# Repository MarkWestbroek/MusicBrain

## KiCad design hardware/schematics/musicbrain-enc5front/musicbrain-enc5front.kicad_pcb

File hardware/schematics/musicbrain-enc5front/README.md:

# MusicBrain ENC5-FRONT — slim front: 5× encoder + 2 knoppen + display-expansie

**Praktisch:** vijf encoders en twee knoppen aan het paneel — de
menu- en parameterbediening van het systeem, via de i2criser aan de
bus.

**Status**: rev 2.0 — ERC 0, netlijst pad-voor-pad geverifieerd, DRC 0/0. Bord **30×110 mm**, 2 lagen.
**Riser**: `musicbrain-i2criser/` (domme I²C-doorlus; de generieke riser past NIET meer — rev 2.0 gebruikt de 1×10-front-koppeling).

## Wat het is

Slim front-bord (route 2): ligt plat aan het paneel, met **2× MCP23017**
(I²C, 32 GPIO-bits) erop. Bedient:

- **5× EC11E-encoder** (verticaal, met drukas — **drukassen zijn bedraad**)
  op de as-hartlijn 8,0 mm, steek **17,6 mm** → paneelknoppen tot ~17 mm;
- **2× drukknopje** (6 mm THT-tact) onder de encoders, ook op de hartlijn;
- **J2 = 2×8 expansieheader** (male, achterzijde) voor het **display-deel**:
  2 extra encoders + 4 knoppen + 2 reservelijnen, via bandkabel.

Dit front zit **uiterst links of rechts** in het paneel: daarom mag het
30 mm breed zijn (i.p.v. de 20 mm-kolom); de as-hartlijn blijft op 8,0.
De encoders zijn 90° gedraaid (pinnenrij horizontaal), zodat de
socketkolom over de hele bordlengte vrij is.

## Koppeling (front-koppel-standaard)

**J1 = 1×10 female socket op de ACHTERZIJDE**, kolom **x = 16,5 mm van de
westrand, pin 1 op 43,57 mm van de bovenrand** — identiek aan pot8front/
jack8/jack4. Contract ENC-front:

| pin | functie |
|----|----|
| 1 | GND |
| 2 | SDA |
| 3 | SCL |
| 4 | /IRQ |
| 5–9 | nc |
| 10 | +3V3 |

## GPIO-toewijzing (firmware-mapping)

**U1 = 0x20** (noord): GPA0–7 = E1A,E1B,E2A,E2B,E3A,E3B,E4A,E4B;
GPB0–3 = E1S..E4S (drukassen), GPB4/5 = X_SP1/X_SP2 (J2-spares), GPB6/7 vrij.

**U2 = 0x21** (zuid): GPA0–7 = X_E6A,X_E6B,X_E6S,X_E7A,X_E7B,X_E7S,X_K1,X_K2;
GPB0/1 = X_K3/X_K4, GPB2/3 = **K1/K2 (knopjes op dit bord)**,
GPB4–6 = E5A,E5B,E5S, GPB7 vrij.

**Firmware**: GPPU aan (alle ingangen, schakelaars schakelen naar GND);
INTA van beide chips deelt /IRQ → **IOCON.ODR = 1 (open-drain) + MIRROR**.

## J2-expansie (display-deel)

| pin | | pin | |
|----|----|----|----|
| 1 | GND | 2 | +3V3 |
| 3 | E6A | 4 | E6B |
| 5 | E6S | 6 | E7A |
| 7 | E7B | 8 | E7S |
| 9 | K1 | 10 | K2 |
| 11 | K3 | 12 | K4 |
| 13 | SP1 | 14 | SP2 |
| 15 | GND | 16 | GND |

(K1..K4/E6/E7 = knoppen/encoders **onder het display**; SP = reserve, op U1.)

## Routing & controlepunten

Koper via de freerouting-pijplijn (DSN → Docker-freerouting → SES native in
de generator), clearance **0,15 mm** (netclass in het .kicad_pro; JLC kan
0,127). X_E7S is een handroute (oostcorridor).

1. ⚠️ **QFN-pinvolgorde** (pin 1 = GPB1, EP = VSS, DS20001952) vóór
   assemblage-order nogmaals tegen de datasheet houden.
2. ⚠️ **Pin-1-oriëntatie** socket ↔ i2criser-J2 bij de eerste fysieke
   passing verifiëren.

## Aansluitoverzicht

### Pinouts

Bovenaanzicht van het bord (kijkend op de pinnen); pin 1 = vierkant. Gegenereerd uit het bordbestand met `hardware/kicad-generators/pinout_svg.py`.

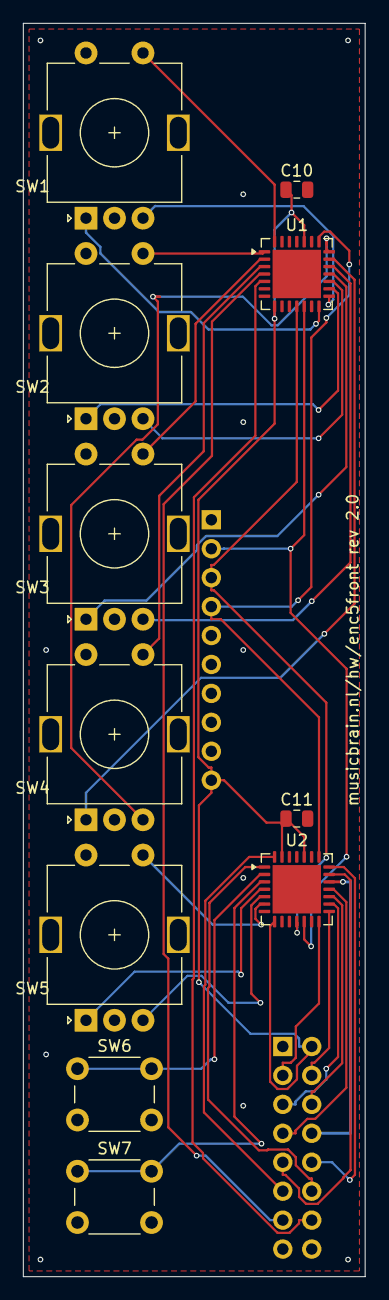
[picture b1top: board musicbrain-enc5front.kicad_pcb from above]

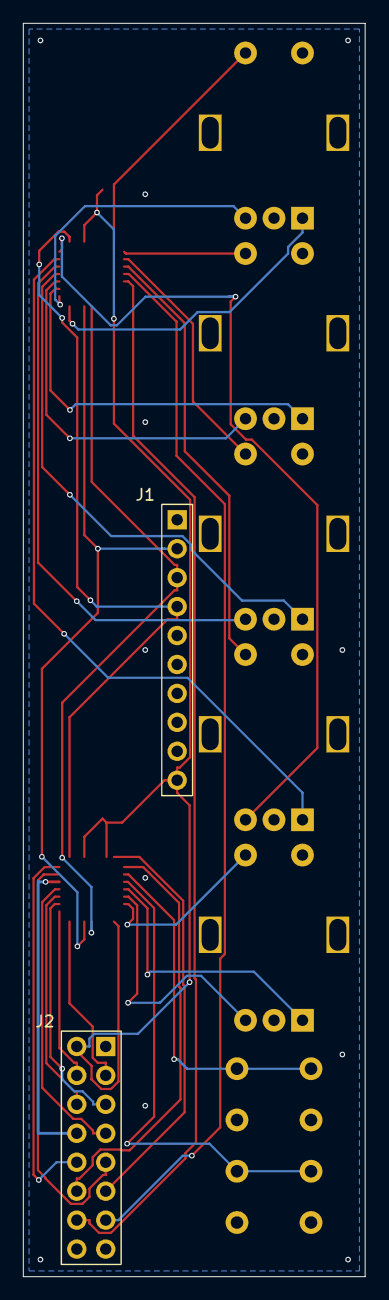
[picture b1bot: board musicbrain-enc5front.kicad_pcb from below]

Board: 2 copper layers, 30.0 x 110.0 mm, 13 parts (2 on the bottom side), 34 nets.

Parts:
C10, C11: 100n; C_0805_2012Metric
J1: Socket_1x10_backside
J2: Header_2x08_backside
SW1, SW2, SW3, SW4, SW5: EC11E; RotaryEncoder_Alps_EC11E-Switch_Vertical_H20mm
SW6, SW7: 6mm tact; SW_PUSH_6mm
U1, U2: MCP23017-E/ML; QFN-28-1EP_6x6mm_P0.65mm_EP4.25x4.25mm

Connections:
+3V3: C10.1, C11.1, J1.10, J2.2, U1.8, U1.24, U2.8, U2.24, U2.27
/E1A: SW1.A, U1.14
/E1B: SW1.B, U1.15
/E1S: SW1.S1, U1.28
/E2A: SW2.A, U1.16
/E2B: SW2.B, U1.17
/E2S: SW2.S1, U1.1
/E3A: SW3.A, U1.18
/E3B: SW3.B, U1.19
/E3S: SW3.S1, U1.2
/E4A: SW4.A, U1.20
/E4B: SW4.B, U1.21
/E4S: SW4.S1, U1.3
/E5A: SW5.A, U2.4
/E5B: SW5.B, U2.5
/E5S: SW5.S1, U2.6
/IRQ: J1.4, U1.22, U2.22
/K1: SW6.1, U2.2
/K2: SW7.1, U2.3
/SCL: J1.3, U1.11, U2.11
/SDA: J1.2, U1.12, U2.12
/X_E6A: J2.3, U2.14
/X_E6B: J2.4, U2.15
/X_E6S: J2.5, U2.16
/X_E7A: J2.6, U2.17
/X_E7B: J2.7, U2.18
/X_E7S: J2.8, U2.19
/X_K1: J2.9, U2.20
/X_K2: J2.10, U2.21
/X_K3: J2.11, U2.28
/X_K4: J2.12, U2.1
/X_SP1: J2.13, U1.4
/X_SP2: J2.14, U1.5
GND: C10.2, C11.2, J1.1, J2.1, J2.15, J2.16, SW1.C, SW1.S2, SW2.C, SW2.S2, SW3.C, SW3.S2, SW4.C, SW4.S2, SW5.C, SW5.S2, SW6.2, SW7.2, U1.9, U1.25, U1.26, U1.27, U1.29, U2.9, U2.25, U2.26, U2.29

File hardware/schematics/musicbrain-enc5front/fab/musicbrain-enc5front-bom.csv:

"Comment","Designator","Footprint","LCSC Part #"
"100n","C10,C11","C_0805_2012Metric","C49678"
"NAAR I2C-RISER (achterzijde)","J1","Socket_1x10_backside",""
"DISPLAY-EXPANSIE (achterzijde)","J2","Header_2x08_backside",""
"EC11E (switch)","SW1,SW2,SW3,SW4,SW5","RotaryEncoder_Alps_EC11E-Switch_Vertical_H20mm",""
"6mm tact","SW6,SW7","SW_PUSH_6mm",""
"MCP23017-E/ML (0x20)","U1","QFN-28-1EP_6x6mm_P0.65mm_EP4.25x4.25mm","C639770"
"MCP23017-E/ML (0x21)","U2","QFN-28-1EP_6x6mm_P0.65mm_EP4.25x4.25mm","C639770"

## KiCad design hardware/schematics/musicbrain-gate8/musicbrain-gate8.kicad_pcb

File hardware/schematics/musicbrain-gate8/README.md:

# MusicBrain GATE8 — 8× gate-uitgang (slotkaart)

**Praktisch:** acht gate/trigger-uitgangen. Start envelopes, klokt
sequencers en triggert extern gear vanuit de software — 0–5 V per
kanaal met serieweerstand. Combineer met een jack8 als front.

**Status**: rev 2.0 — ERC 0, netlijst pad-voor-pad geverifieerd, DRC 0/0.
**Spec**: `doc/spi-bus-spec.md` v2.0. Bord **55 × 45 mm**, 2 lagen.

## Gen 2 (rev 2.0, 2026-07-16)

- Slot **2×12**; H 80 → 45; 74HCT595 met de Q-uitgangen noordwaarts
  naar de 1k-kolommen. J2-contract en bitvolgorde ongewijzigd.
- Generator geport naar cardlib (`gen_gate.py`); koper via freerouting.

De schakelingbeschrijving hieronder is ongewijzigd; waar de lopende
tekst nog gen-1-maten of 2×10 noemt, geldt bovenstaande. Overzicht en
pinouts hieronder zijn gen-2-gegenereerd.

## Wat het is

De simpelste kaart van de familie: 8 digitale gate/trigger-uitgangen (0–5V)
uit één **74HCT595 schuifregister**. Geen microcontroller nodig — SPI *is*
een schuifregisterprotocol, dus de 595 is zelf de ontvanger:

| 595-pin | Buslijn | Werking |
|---|---|---|
| SER (14) | MOSI | databits schuiven binnen |
| SRCLK (11) | SCLK | klok per bit |
| RCLK (12) | CS (slotpin 13) | **stijgende flank van CS** kopieert alle 8 bits tegelijk naar de uitgangen |
| ~OE (13) | GND | uitgangen altijd actief |
| ~SRCLR (10) | +5V | nooit hardware-clear |

Firmware: `SPI.beginTransaction(mode 0)` → CS laag → `SPI.transfer(bits)` →
CS hoog → alle acht gates staan er glitch-vrij en gelijktijdig op.
Bit 0 = QA = GATE1 … bit 7 = QH = GATE8.

## Ontwerpkeuzes

- **HCT-variant op 5V**: TTL-drempels, dus de 3,3V-bussignalen zijn ruim
  voldoende, terwijl de uitgangen echte 0–5V gates leveren (Eurorack-drempel
  ~1–2V). De 5V komt lokaal van een AMS1117-5.0 uit de +12V-rail.
- **1 kΩ serie per uitgang**: kortsluit-/kabelbescherming.
- Buspinnen MISO, LDAC, I2C, IRQ, SPARE's en −12V zijn bewust niet
  aangesloten (write-only kaart).
- SPI-mode 0 (de AD5754 gebruikt mode 1 — de Teensy wisselt per transactie
  via `SPISettings`, zie spec regel 4).

## Aansluitingen

- **J1** (haakse male 2×10, onderrand): het bus-slotcontract uit de spec.
  Pennen steken 6 mm onder de kaartrand uit, het slot-socket in.
- **J2** (haakse male 1×10, bovenrand): 1 = GND, 2–9 = GATE1..8, 10 = GND.
  Zelfde contract als de ADC8-kaart → één jack8-printje past op beide.
  J2 staat **recht boven het midden van J1** (spec-standaard), zodat de
  jack-strips van alle kaarten op de bovenplaat uitlijnen.

## PCB-notities (v1.1)

Signaalstroom van onder naar boven: J1 (bus) → 74HCT595 → weerstandsrij →
J2 (paneel). De Q-uitgangen verlaten de chip via een via-kolom en lopen als
L-paden over B.Cu (oost, dan noord) naar hun weerstand — exits en doelen
staan in dezelfde volgorde, dus dat is kruisingsvrij; QA komt van de
oostkolom en loopt bovenlangs om de "Q-wal" heen. SCLK en CS hebben elk
één B.Cu-hop om de aanvoer vanaf J1 te ontvlechten. De AMS1117 met C1–C3
zit in de zuidoosthoek; +5V loopt via één B.Cu-run (y=157,5) naar VCC,
~SRCLR en de condensatoren. GND via vlakken op beide lagen + stitching-via's.

## Uitbreidingsideeën (v2)

- LED + weerstand per gate (visuele feedback).
- TPIC6B595 i.p.v. HCT595 voor 10V-gates of zwaardere belasting.
- Tweede 595 in ketting (QH' → SER) voor 16 gates met dezelfde CS.

## Aansluitoverzicht

### Pinouts

Bovenaanzicht van het bord (kijkend op de pinnen); pin 1 = vierkant. Gegenereerd uit het bordbestand met `hardware/kicad-generators/pinout_svg.py`.

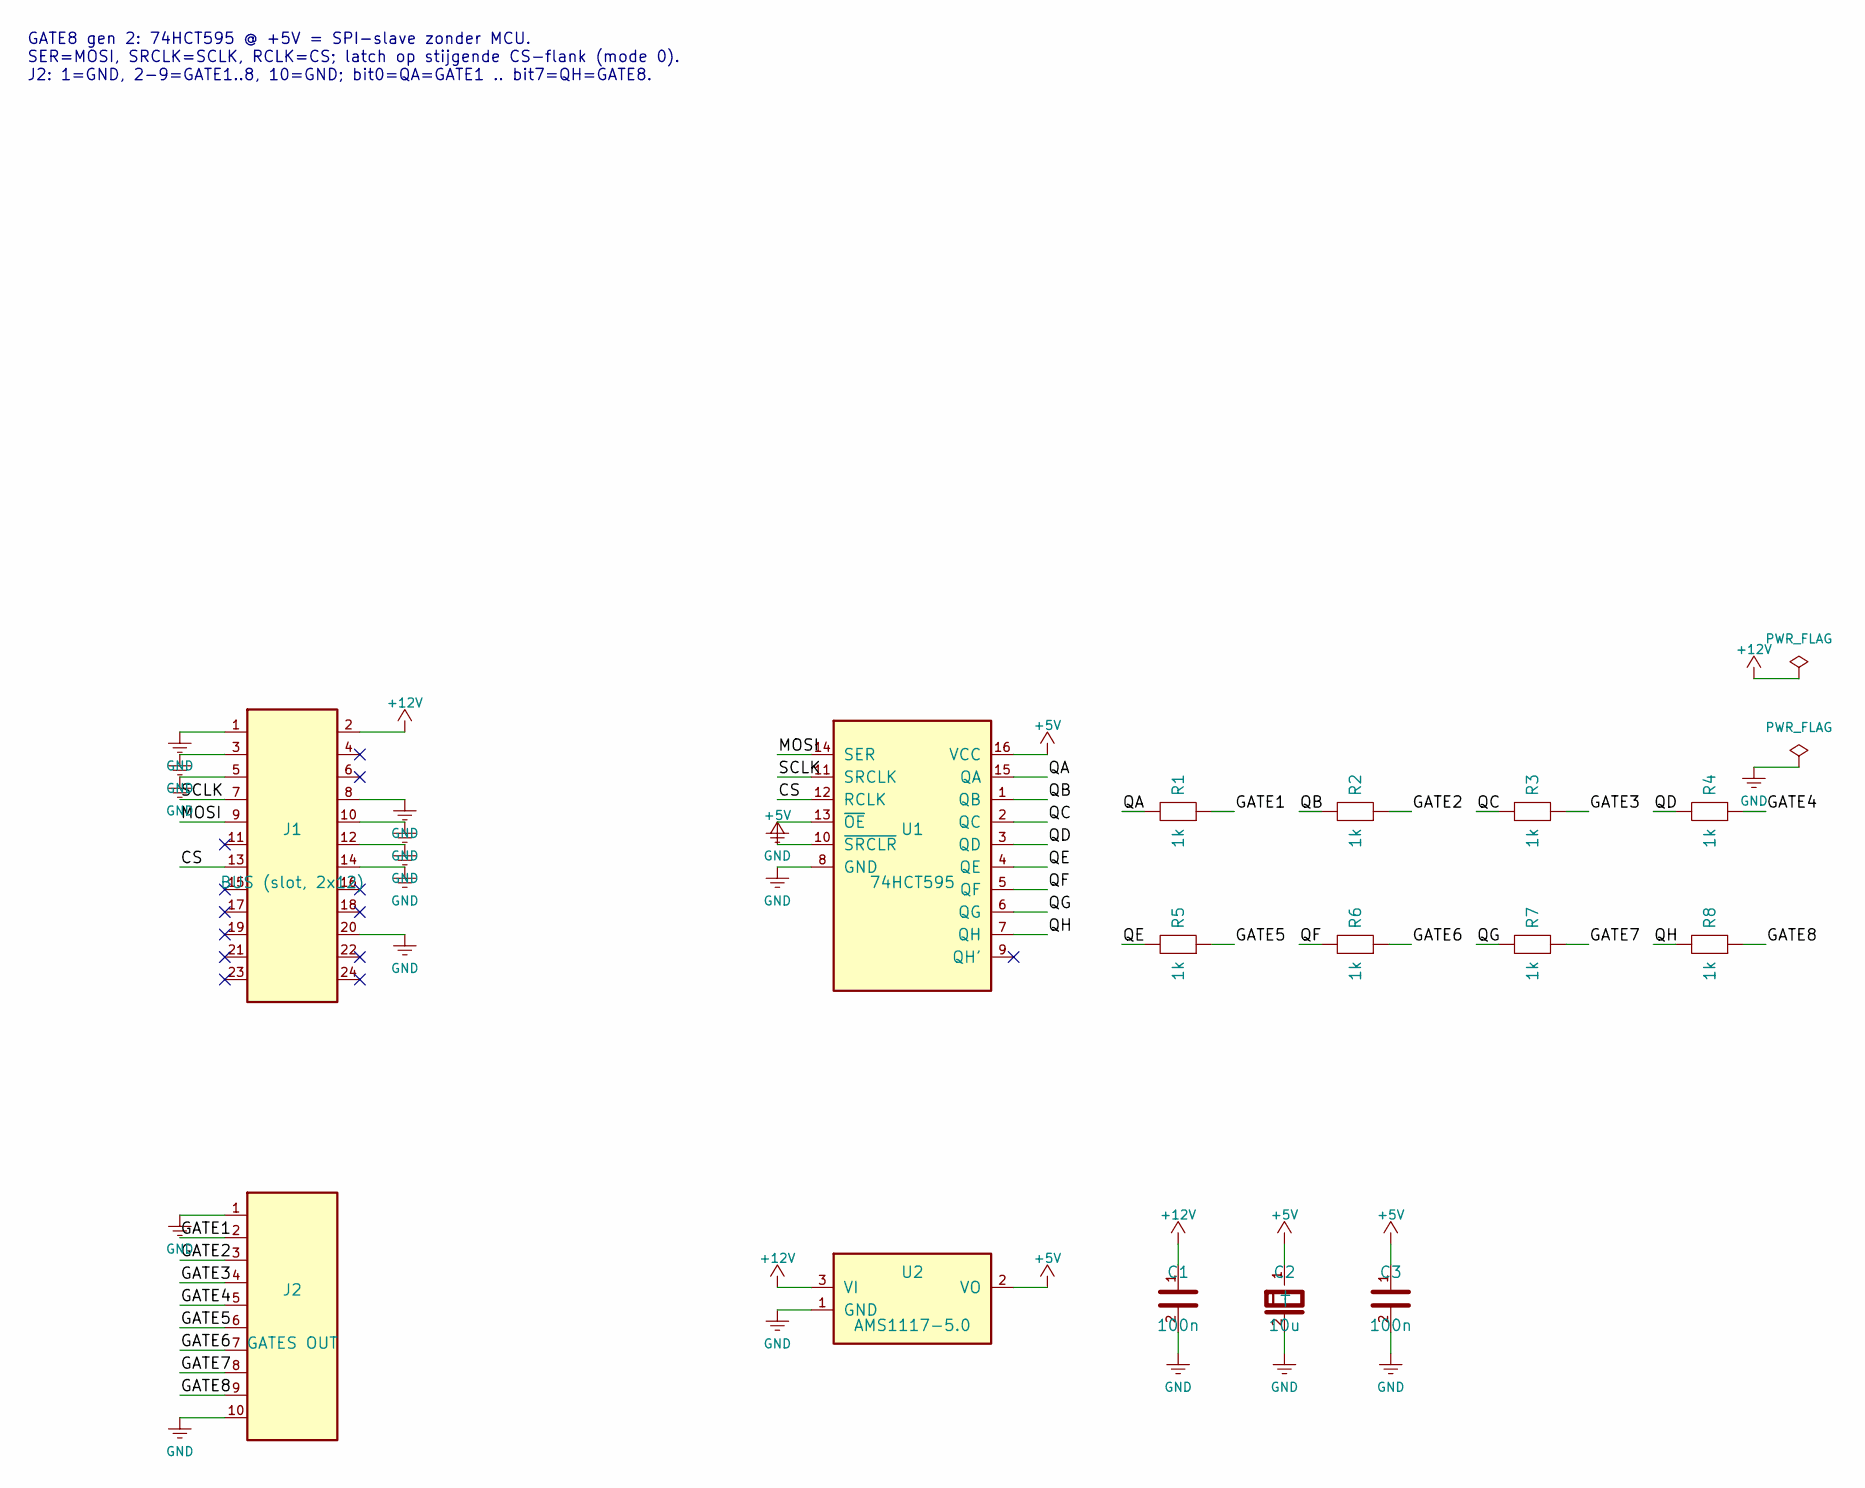
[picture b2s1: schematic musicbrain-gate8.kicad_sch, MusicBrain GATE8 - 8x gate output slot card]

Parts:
C1, C3: 100n; C_0805_2012Metric
C2: 10u; CP_Elec_4x5.3
J1: BUS (slot, 2x12); PinHeader_2x12_P2.54mm_Horizontal
J2: GATES OUT; PinHeader_1x10_P2.54mm_Horizontal
R1, R2, R3, R4, R5, R6, R7, R8: 1k; R_0805_2012Metric
U1: 74HCT595; SOIC-16_3.9x9.9mm_P1.27mm
U2: AMS1117-5.0; SOT-223-3_TabPin2

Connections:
+5V: C2.1 (+), C3.1, U1.10 (~SRCLR), U1.16 (VCC), U2.2 (VO)
+12V: C1.1, J1.2, U2.3 (VI)
/CS: J1.13, U1.12 (RCLK)
/GATE1: J2.2, R1.2
/GATE2: J2.3, R2.2
/GATE3: J2.4, R3.2
/GATE4: J2.5, R4.2
/GATE5: J2.6, R5.2
/GATE6: J2.7, R6.2
/GATE7: J2.8, R7.2
/GATE8: J2.9, R8.2
/MOSI: J1.9, U1.14 (SER)
/QA: R1.1, U1.15 (QA)
/QB: R2.1, U1.1 (QB)
/QC: R3.1, U1.2 (QC)
/QD: R4.1, U1.3 (QD)
/QE: R5.1, U1.4 (QE)
/QF: R6.1, U1.5 (QF)
/QG: R7.1, U1.6 (QG)
/QH: R8.1, U1.7 (QH)
/SCLK: J1.7, U1.11 (SRCLK)
GND: C1.2, C2.2 (-), C3.2, J1.1, J1.3, J1.5, J1.8, J1.10, J1.12, J1.14, J1.20, J2.1, J2.10, U1.8 (GND), U1.13 (~OE), U2.1 (GND)

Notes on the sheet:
GATE8 gen 2: 74HCT595 @ +5V = SPI-slave zonder MCU. SER=MOSI, SRCLK=SCLK, RCLK=CS; latch op stijgende CS-flank (mode 0). J2: 1=GND, 2-9=GATE1..8, 10=GND; bit0=QA=GATE1 .. bit7=QH=GATE8.

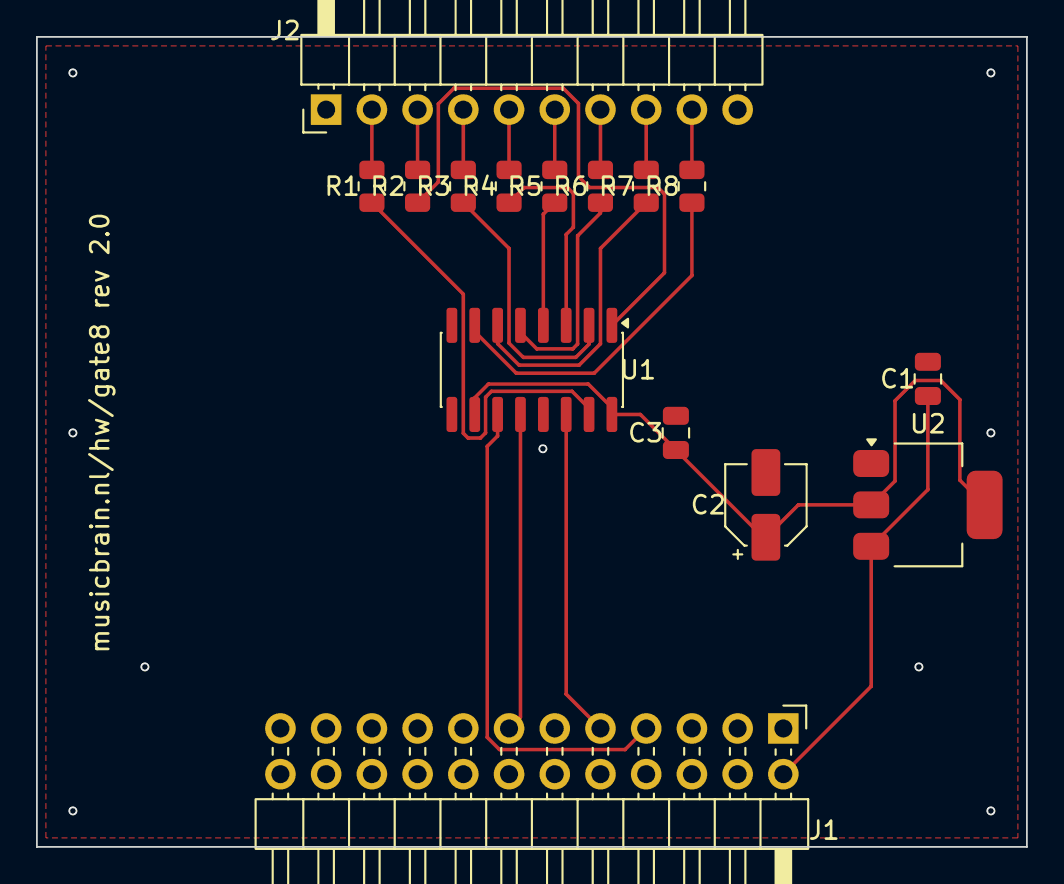
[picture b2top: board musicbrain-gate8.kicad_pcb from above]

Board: 2 copper layers, 55.0 x 45.0 mm, 15 parts (0 on the bottom side), 22 nets.

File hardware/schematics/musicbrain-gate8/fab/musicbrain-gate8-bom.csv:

"Comment","Designator","Footprint","LCSC Part #"
"100n","C1,C3","C_0805_2012Metric","C49678"
"10u","C2","CP_Elec_4x5.3",""
"BUS","J1","PinHeader_2x10_P2.54mm_Horizontal",""
"GATES OUT","J2","PinHeader_1x10_P2.54mm_Horizontal",""
"1k","R1,R2,R3,R4,R5,R6,R7,R8","R_0805_2012Metric","C17513"
"74HCT595","U1","SOIC-16_3.9x9.9mm_P1.27mm","C282339"
"AMS1117-5.0","U2","SOT-223-3_TabPin2","C6187"

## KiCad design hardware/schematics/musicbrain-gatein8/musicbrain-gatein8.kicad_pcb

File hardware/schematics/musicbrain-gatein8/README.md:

# MusicBrain GATEIN8 — 8× gate/trigger-ingang (slotkaart)

**Praktisch:** acht gate/trigger-ingangen. Leest externe klokken,
triggers en voetschakelaars de software in, met ingangsbeveiliging en
een gedefinieerd rustniveau per kanaal. Combineer met een jack8.

**Status**: rev 2.0 — ERC 0, netlijst pad-voor-pad geverifieerd, DRC 0/0.
**Spec**: `doc/spi-bus-spec.md` v2.0. Bord **50 × 45 mm**, 2 lagen.

## Gen 2 (rev 2.0, 2026-07-16)

- Slot **2×12** via `bus.j1_map`; H 80 → 45; kanaalkolommen recht onder
  de J2-pinnen. D_OF_IN-mapping (firmware-contract) ongewijzigd.
- Koper via freerouting; GND via de vlakken + hechtvia's.

De schakelingbeschrijving hieronder is ongewijzigd; waar de lopende
tekst nog gen-1-maten of 2×10 noemt, geldt bovenstaande. Overzicht en
pinouts hieronder zijn gen-2-gegenereerd.

## Wat het is

8 digitale ingangen (gates, triggers, clocks) die de firmware in één
SPI-transactie binnenhaalt via een **74HC165** schuifregister (parallel-in,
serieel-uit) op +3V3. Elke ingang is Eurorack-proof geconditioneerd:

- **100 kΩ serie** (R1–R8): stroombegrenzing bij hete signalen;
- **100 kΩ pulldown** (R11–R18): ongepatcht = netjes laag;
- **BAT54S-clamp** (D1–D8): knoop geklemd tussen GND en +3V3 — ±10V mag
  er zo in (≤ ~70 µA clampstroom door de 100k).
- HC-drempel op 3V3 ≈ 1,65 V → alles boven ~2 V telt als hoog.

## Latch-truc (~PL vanaf CS)

De '165 laadt parallel zolang ~PL laag is en schuift pas als hij weer
hoog is — maar CS blijft laag tijdens de hele SPI-transactie. Daarom maakt
**C3 (220p) + R9 (10k naar 3V3)** van de CS-neerflank een korte
~PL-latchpuls (~2 µs): de kaart bevriest zijn 8 bits op CS↓, daarna klokt
de Teensy ze binnen. **Firmware: wacht ≥5 µs tussen CS-laag en de
transfer.** Q7 gaat via een **74LVC1G125** (OE = CS) naar MISO, zodat de
kaart de bus loslaat als hij niet geselecteerd is.

## Bitvolgorde

Routinggedreven mapping (firmware hertelt met een tabel), eerste bit
(Q7/D7) eerst: **IN6, IN5, IN4, IN3, IN1, IN2, IN7, IN8**.

## Aansluitingen

- **J1** (haakse male 2×10, onderrand): bus-slotcontract; alleen SCLK,
  MISO, CS en +3V3 gebruikt — MOSI/±12V nc.
- **J2** (haakse male 1×10, bovenrand): 1 = GND, 2–9 = IN1..8, 10 = GND —
  zelfde contract als GATE8/ADC8, dus hetzelfde jack8-printje past.
  **JP1 op het jack8-printje dichtsolderen** (inputs → ongepatcht 0 V).

## PCB-notities

Per kanaal een knoopkolom onder de serieweerstand: pulldown-tap opzij,
diode-pad-3 op de kolom (het spoor duikt tussen de diodepads 1/2 door).
De acht knopen bereiken de '165 via B.Cu-lanes: vier bovenlangs
(y 129–131,4) naar de noordrij, vier onderlangs (y 145–147,4) dwars
tussen de SOIC-padrijen door naar de zuidrij. De +3V3-spine loopt langs
de oostrand met B-aftakrijen voor de diodes (y 122,9/127,3), VCC (132,9)
en R9 (148,9). MISO duikt onder de J1-padrij door (B.Cu) het THT-pad in.

## Aansluitoverzicht

### Pinouts

Bovenaanzicht van het bord (kijkend op de pinnen); pin 1 = vierkant. Gegenereerd uit het bordbestand met `hardware/kicad-generators/pinout_svg.py`.

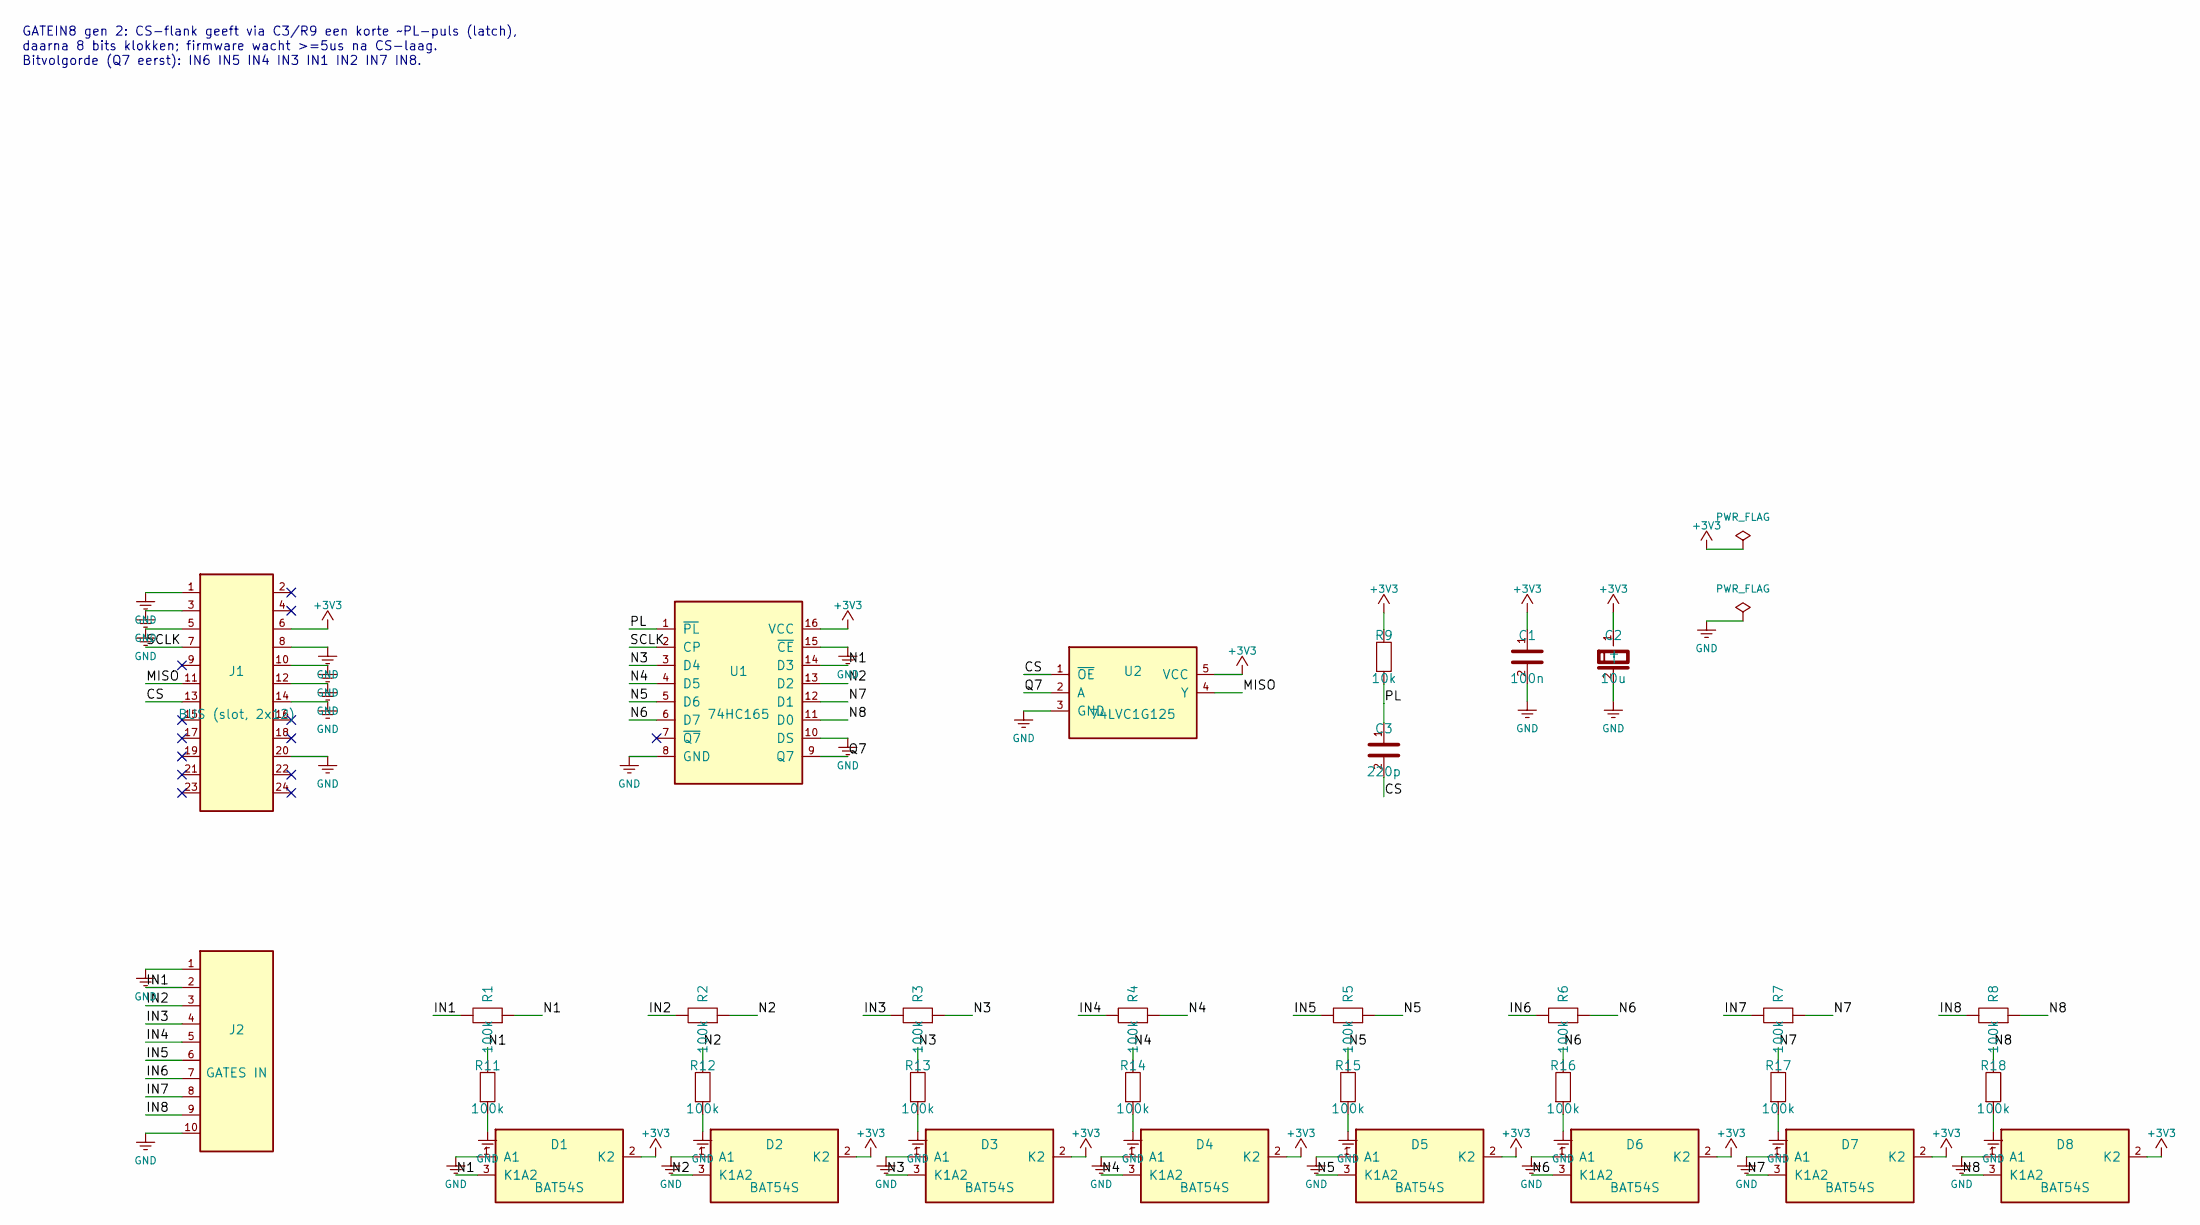
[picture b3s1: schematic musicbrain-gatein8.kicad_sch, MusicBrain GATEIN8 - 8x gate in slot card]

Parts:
C1: 100n; C_0805_2012Metric
C2: 10u; CP_Elec_4x5.3
C3: 220p; C_0805_2012Metric
D1, D2, D3, D4, D5, D6, D7, D8: BAT54S; SOT-23
J1: BUS (slot, 2x12); PinHeader_2x12_P2.54mm_Horizontal
J2: GATES IN; PinHeader_1x10_P2.54mm_Horizontal
R1, R2, R3, R4, R5, R6, R7, R8, R11, R12, R13, R14, R15, R16, R17, R18: 100k; R_0805_2012Metric
R9: 10k; R_0805_2012Metric
U1: 74HC165; SOIC-16_3.9x9.9mm_P1.27mm
U2: 74LVC1G125; SOT-23-5

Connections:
+3V3: C1.1, C2.1 (+), D1.2 (K2), D2.2 (K2), D3.2 (K2), D4.2 (K2), D5.2 (K2), D6.2 (K2), D7.2 (K2), D8.2 (K2), J1.6, R9.1, U1.16 (VCC), U2.5 (VCC)
/CS: C3.2, J1.13, U2.1 (~OE)
/IN1: J2.2, R1.1
/IN2: J2.3, R2.1
/IN3: J2.4, R3.1
/IN4: J2.5, R4.1
/IN5: J2.6, R5.1
/IN6: J2.7, R6.1
/IN7: J2.8, R7.1
/IN8: J2.9, R8.1
/MISO: J1.11, U2.4 (Y)
/N1: D1.3 (K1A2), R1.2, R11.1, U1.14 (D3)
/N2: D2.3 (K1A2), R2.2, R12.1, U1.13 (D2)
/N3: D3.3 (K1A2), R3.2, R13.1, U1.3 (D4)
/N4: D4.3 (K1A2), R4.2, R14.1, U1.4 (D5)
/N5: D5.3 (K1A2), R5.2, R15.1, U1.5 (D6)
/N6: D6.3 (K1A2), R6.2, R16.1, U1.6 (D7)
/N7: D7.3 (K1A2), R7.2, R17.1, U1.12 (D1)
/N8: D8.3 (K1A2), R8.2, R18.1, U1.11 (D0)
/PL: C3.1, R9.2, U1.1 (~PL)
/Q7: U1.9 (Q7), U2.2 (A)
/SCLK: J1.7, U1.2 (CP)
GND: C1.2, C2.2 (-), D1.1 (A1), D2.1 (A1), D3.1 (A1), D4.1 (A1), D5.1 (A1), D6.1 (A1), D7.1 (A1), D8.1 (A1), J1.1, J1.3, J1.5, J1.8, J1.10, J1.12, J1.14, J1.20, J2.1, J2.10, R11.2, R12.2, R13.2, R14.2, R15.2, R16.2, R17.2, R18.2, U1.8 (GND), U1.10 (DS), U1.15 (~CE), U2.3 (GND)

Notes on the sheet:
GATEIN8 gen 2: CS-flank geeft via C3/R9 een korte ~PL-puls (latch), daarna 8 bits klokken; firmware wacht >=5us na CS-laag. Bitvolgorde (Q7 eerst): IN6 IN5 IN4 IN3 IN1 IN2 IN7 IN8.

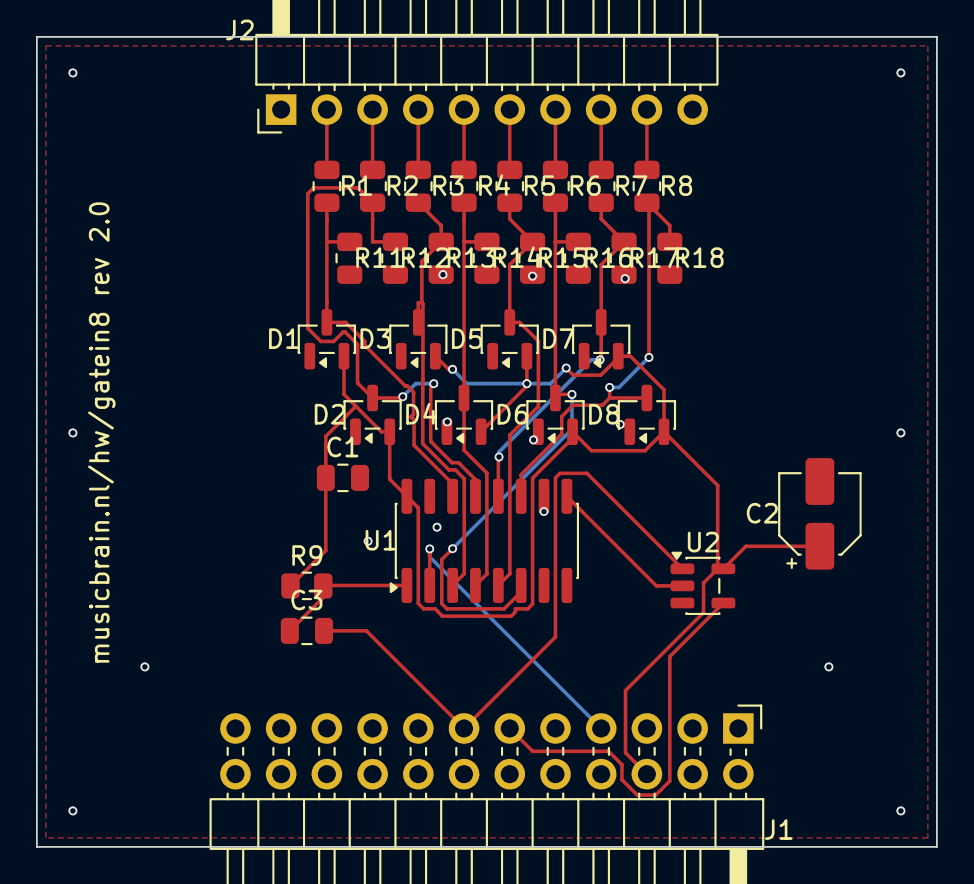
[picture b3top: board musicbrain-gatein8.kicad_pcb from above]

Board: 2 copper layers, 50.0 x 45.0 mm, 32 parts (0 on the bottom side), 23 nets.

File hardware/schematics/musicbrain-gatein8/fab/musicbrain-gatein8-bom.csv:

"Comment","Designator","Footprint","LCSC Part #"
"100n","C1","C_0805_2012Metric","C49678"
"10u","C2","CP_Elec_4x5.3","C3343"
"220p","C3","C_0805_2012Metric","C107145"
"BAT54S","D1,D2,D3,D4,D5,D6,D7,D8","SOT-23","C7420333"
"BUS","J1","PinHeader_2x10_P2.54mm_Horizontal","C19190505"
"GATES IN","J2","PinHeader_1x10_P2.54mm_Horizontal","C2687688"
"100k","R1,R2,R3,R4,R5,R6,R7,R8,R11,R12,R13,R14,R15,R16,R17,R18","R_0805_2012Metric","C149504"
"10k","R9","R_0805_2012Metric","C17414"
"74HC165","U1","SOIC-16_3.9x9.9mm_P1.27mm","C5613"
"74LVC1G125","U2","SOT-23-5","C12518"

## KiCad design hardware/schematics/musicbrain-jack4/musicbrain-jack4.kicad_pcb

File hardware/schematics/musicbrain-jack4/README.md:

# MusicBrain jack4 — Thonkiconn-paneeldrager (4 jacks)

**Praktisch:** 4-kanaals jack-breakout aan een kabel, voor CV-uit via
een hub-connector (bijv. de AD5754-breakout) — kost geen slot.

**Status**: rev 2.0 — ERC 0, netlijst geverifieerd, DRC 0/0. Bord **20 × 60 mm**.

## Gen 2 (rev 2.0, 2026-07-16)

- 4 jacks op steek **13,75**; kabelbord aan de hub-DAC (centrering van de
  socket is hier niet relevant).
- Zelfde pad-slanking en randmarge als jack8.

De schakelingbeschrijving hieronder is ongewijzigd; waar de lopende
tekst nog gen-1-maten of 2×10 noemt, geldt bovenstaande. Overzicht en
pinouts hieronder zijn gen-2-gegenereerd.
**Zusje: `musicbrain-jack8/` (8 jacks + 1×10 header).**

**v1.2 (2026-07-11)**: socket op de **front-koppel-standaard** (kolom x = 16,5
van de westrand, pin 1 op 43,57 van de bovenrand); 3D-model op de gatenrij;
silk-URL naar bordmidden; PCB-papier A3.

## Wat het is

Een passieve strip met **4× Thonkiconn** (PJ398SM = PJ301M-12 = WQP518MA,
onderling uitwisselbaar) op 15 mm steek, die als **frontpaneel-drager**
dient: de strip ligt horizontaal onder de bovenplaat, de schroefbussen steken erdoorheen en de moeren klemmen paneel
en printje op elkaar — geen extra steunen nodig.

## Aansluiting op de kaarten

- **J1** (1×6): 1 = GND, 2–5 = CH1..4, 6 = GND — hetzelfde contract als
  J2 op GATE8 én ADC8, dus één jack4 past op beide kaartsoorten.
- **Montage**: de female socket wordt op de **achterzijde** gesoldeerd
  (opening richting kaart); de kaart krijgt aan zijn frontrand een haakse
  male header. Het silkscreen op de achterzijde markeert de positie.
- Headerpositie: hart in het **midden van de strip**; de kaart heeft zijn
  paneelconnector recht boven het slotcentrum (spec-standaard), zodat elk
  jack-printje op elke kaart past en de strips op de bovenplaat uitlijnen.

## JP1: schakelcontact-normalling

Elke Thonkiconn heeft een schakelcontact (TN) dat bij een ongepatchte jack
tegen de tip ligt. Alle TN's zijn gebust naar één soldeerjumper **JP1**:

- **INPUT-kaart (ADC8): JP1 dichtsolderen** → ongepatchte ingangen lezen
  netjes 0 V.
- **OUTPUT-kaart (GATE8/DAC): JP1 OPEN laten!** Anders wordt elke
  ongepatchte uitgang via het schakelcontact naar GND kortgesloten
  (de 100R/1k serieweerstanden beperken dat, maar het hoort niet).

## Paneel

3U Eurorack: paneelhoogte 128,5 mm; boorpatroon = 4× Ø6 mm gat op 15 mm
steek, gecentreerd op de jackposities (eerste jack 8 mm van de bovenrand
van het printje). Printje zelf is 65 mm hoog (half 3U-paneel of 3U half gevuld).

## Aansluitoverzicht

### Pinouts

Bovenaanzicht van het bord (kijkend op de pinnen); pin 1 = vierkant. Gegenereerd uit het bordbestand met `hardware/kicad-generators/pinout_svg.py`.

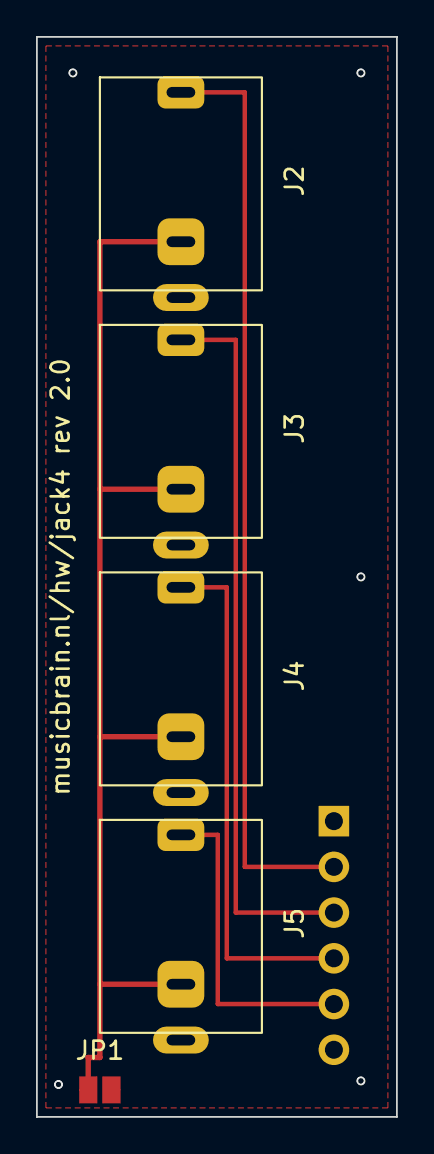
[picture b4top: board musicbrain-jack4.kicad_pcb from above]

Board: 2 copper layers, 20.0 x 60.0 mm, 6 parts (1 on the bottom side), 6 nets.

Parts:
J1: SOCKET-BACK; Header_1x06_backside
J2, J3, J4, J5: PJ398SM; Jack_3.5mm_PJ398SM_Thonkiconn
JP1: NORM=GND; SolderJumper-2_P1.3mm_Open_TrianglePad1.0x1.5mm

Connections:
/CH1: J1.2, J2.1
/CH2: J1.3, J3.1
/CH3: J1.4, J4.1
/CH4: J1.5, J5.1
/NORM: J2.3, J3.3, J4.3, J5.3, JP1.1
GND: J1.1, J1.6, J2.2, J3.2, J4.2, J5.2, JP1.2

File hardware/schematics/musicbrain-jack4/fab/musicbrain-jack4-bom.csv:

"Comment","Designator","Footprint","LCSC Part #"
"NAAR KAART","J1","PinSocket_1x06_P2.54mm_Vertical","C124415"
"PJ398SM","J2,J3,J4,J5","Jack_3.5mm_PJ398SM_Thonkiconn",""
